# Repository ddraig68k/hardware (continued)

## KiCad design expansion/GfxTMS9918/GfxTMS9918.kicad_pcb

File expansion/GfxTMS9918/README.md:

# TMS9918 Video card

The TMS9918A is capable of a 256x192 pixel display with a 15 colour palette. It has 16K of video memory and 4 different video modes.

From the [Sega Retro](https://segaretro.org/TMS9918) site:

>There are 4 different screen modes available in the TMS9918A (as mentioned before, the TMS9918 lacks mode Graphic II):
>
>Mode 0 (Text): 40×24 characters monochrome. As the display is 256 pixels width, the character set is only 6 pixels wide. This mode doesn't support sprites, nor a separate border color setting.
>
>Mode 1 (Graphic 1): 32×24 characters (256×192 bitmap), where for each 8 characters in the character set the foreground and background color can be set. The chars "0"-"7" for example all have the same attributes.
>
>Mode 2 (Graphic 2): 32×24 characters (256×192 bitmap), with a 2-color limitation for each 8 pixel wide line inside a character.
>
>Mode 3 (Multicolor): 64×48 mode, very blocky and rarely used. Each 'pixel' can have its own color defined though, hence the name. Its sprites still have the same resolution as in screen modes 1 and 2.
>
>The TMS9918 has a fixed 16-color palette (actually 15 colors + transparent). 

The TMS9918A was designed to use DRAM, but I have used the design by [Leonardo Miliani](https://www.leonardomiliani.com/en/2019/lm80c-tms9918a/) that allows SRAM to be used instead.

The TMS9918 can also display up to 32 sprites (4 per scanline).

[Plasma effect on the TMS9918](https://www.youtube.com/watch?v=u6DVTGFEivY)

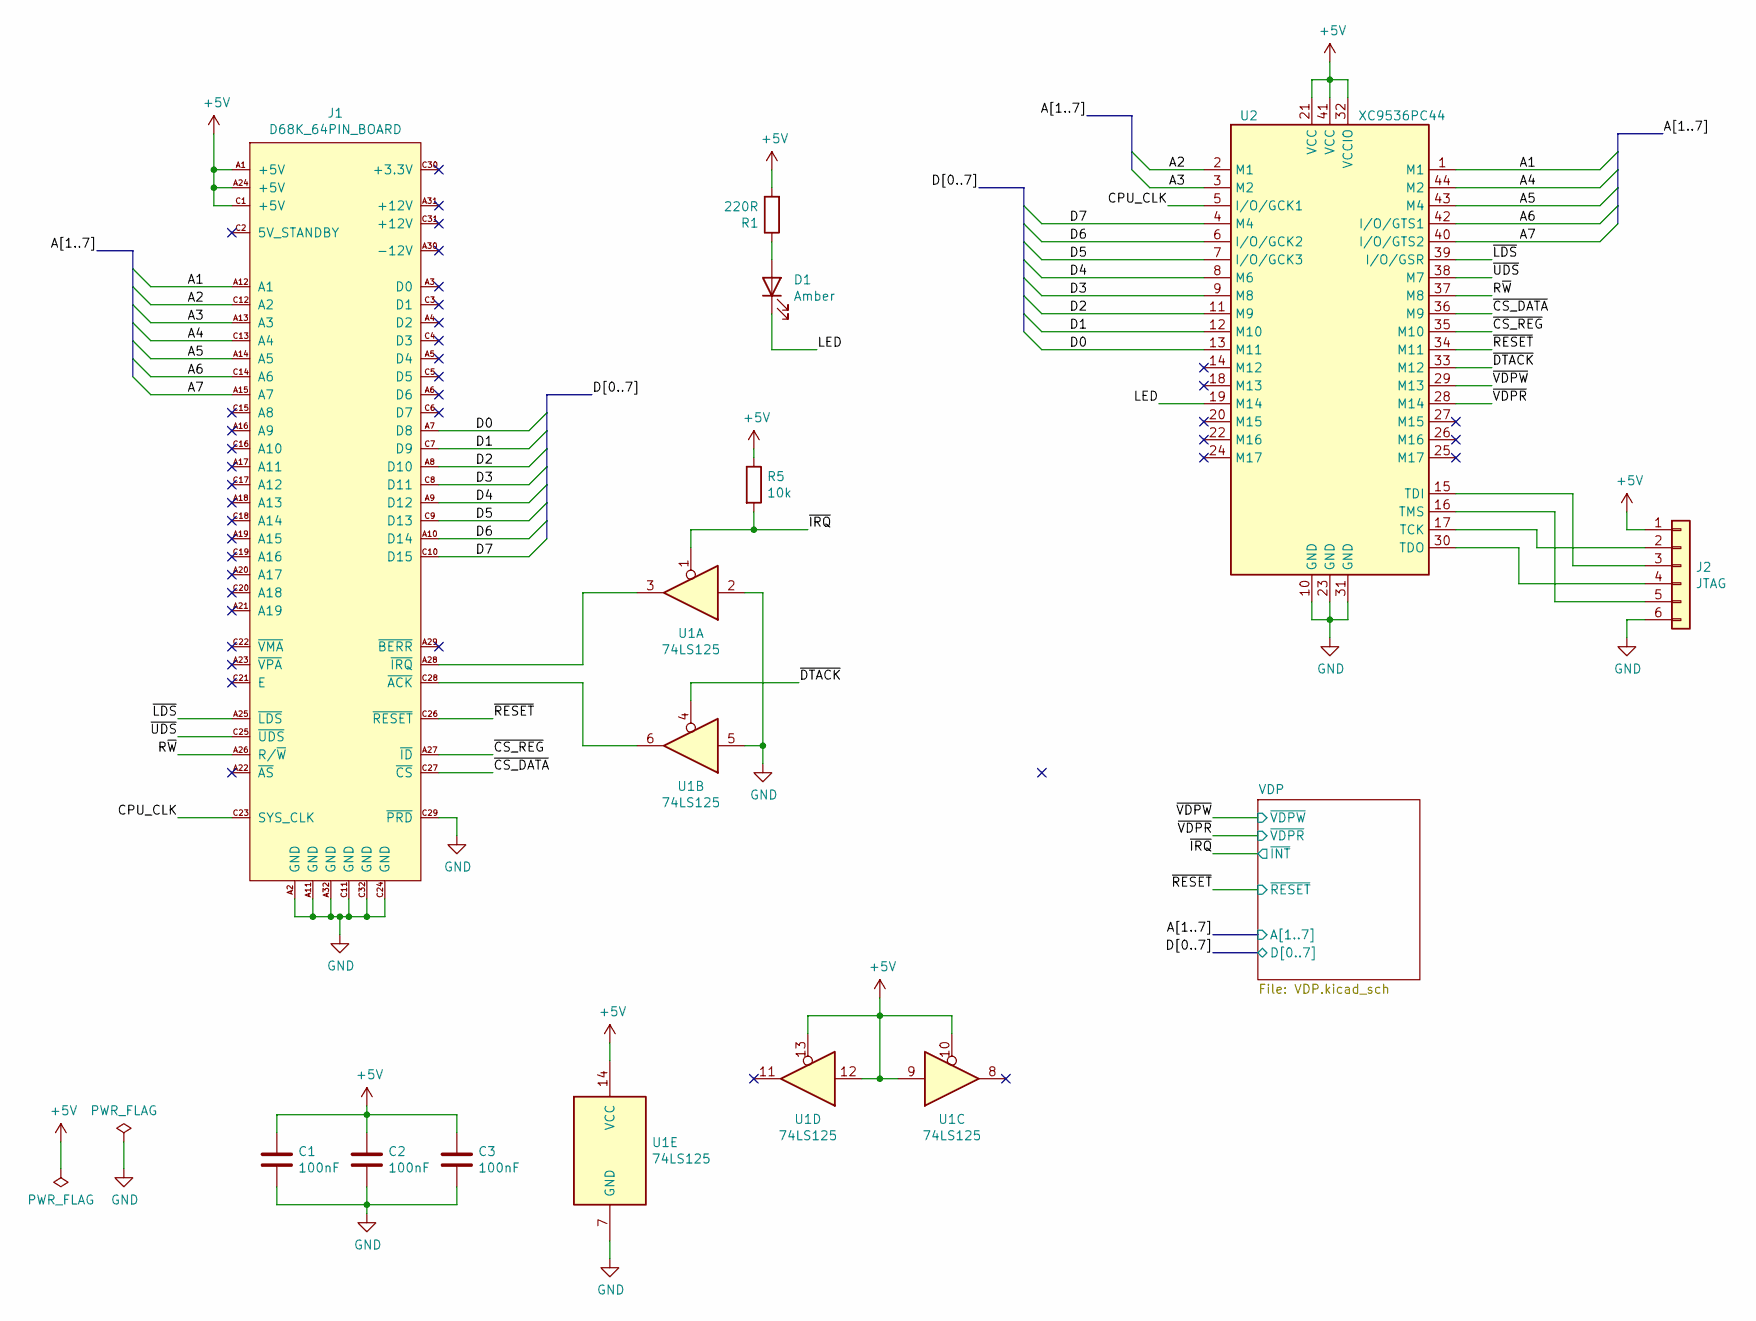
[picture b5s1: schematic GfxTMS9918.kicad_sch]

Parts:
C1, C2, C3: 100nF; C_Disc_D5.0mm_W2.5mm_P2.50mm
D1: Amber; LED_D5.0mm_FlatTop
J1: D68K_64PIN_BOARD; DIN41612_C_2x32_Male_Horizontal_THT
J2: JTAG; PinHeader_1x06_P2.54mm_Vertical
R1: 220R; R_Axial_DIN0207_L6.3mm_D2.5mm_P10.16mm_Horizontal
R5: 10k; R_Axial_DIN0207_L6.3mm_D2.5mm_P10.16mm_Horizontal
U1: 74LS125; DIP-14_W7.62mm_Socket
U2: XC9536PC44; PLCC-44_THT-Socket

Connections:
+5V: C1.1, C2.1, C3.1, J1.A1 (+5V), J1.A24 (+5V), J1.C1 (+5V), J2.1, R1.2, R5.1, U1.9, U1.10, U1.12, U1.13, U1.14 (VCC), U2.21 (VCC), U2.32 (VCCIO), U2.41 (VCC); also elsewhere on the board
/A1: J1.A12 (A1), U2.1 (M1); also elsewhere on the board
/A2: J1.C12 (A2), U2.2 (M1)
/A3: J1.A13 (A3), U2.3 (M2)
/A4: J1.C13 (A4), U2.44 (M2)
/A5: J1.A14 (A5), U2.43 (M4)
/A6: J1.C14 (A6), U2.42 (I/O/GTS1)
/A7: J1.A15 (A7), U2.40 (I/O/GTS2)
/CPU_CLK: J1.C23 (SYS_CLK), U2.5 (I/O/GCK1)
/D0: J1.A7 (D8), U2.13 (M11); also elsewhere on the board
/D1: J1.C7 (D9), U2.12 (M10); also elsewhere on the board
/D2: J1.A8 (D10), U2.11 (M9); also elsewhere on the board
/D3: J1.C8 (D11), U2.9 (M8); also elsewhere on the board
/D4: J1.A9 (D12), U2.8 (M6); also elsewhere on the board
/D5: J1.C9 (D13), U2.7 (I/O/GCK3); also elsewhere on the board
/D6: J1.A10 (D14), U2.6 (I/O/GCK2); also elsewhere on the board
/D7: J1.C10 (D15), U2.4 (M4); also elsewhere on the board
/LED: D1.1 (K), U2.19 (M14)
/R~W: J1.A26 (R/~W), U2.37 (M8)
/~CS_DATA: J1.C27 (~CS), U2.36 (M9)
/~CS_REG: J1.A27 (~ID), U2.35 (M10)
/~DTACK: U1.4, U2.33 (M12)
/~IRQ: R5.2, U1.1; also elsewhere on the board
/~LDS: J1.A25 (~LDS), U2.39 (I/O/GSR)
/~RESET: J1.C26 (~RESET), U2.34 (M11); also elsewhere on the board
/~UDS: J1.C25 (~UDS), U2.38 (M7)
/~VDPR: U2.28 (M14); also elsewhere on the board
/~VDPW: U2.29 (M13); also elsewhere on the board
GND: C1.2, C2.2, C3.2, J1.A2 (GND), J1.A11 (GND), J1.A32 (GND), J1.C11 (GND), J1.C24 (GND), J1.C29 (~PRD), J1.C32 (GND), J2.6, U1.2, U1.5, U1.7 (GND), U2.10 (GND), U2.23 (GND), U2.31 (GND); also elsewhere on the board
unnamed: D1.2 (A), R1.1
unnamed: J1.A28 (~IRQ), U1.3
unnamed: J1.C28 (~ACK), U1.6
unnamed: J2.2, U2.17 (TCK)
unnamed: J2.3, U2.15 (TDI)
unnamed: J2.4, U2.30 (TDO)
unnamed: J2.5, U2.16 (TMS)

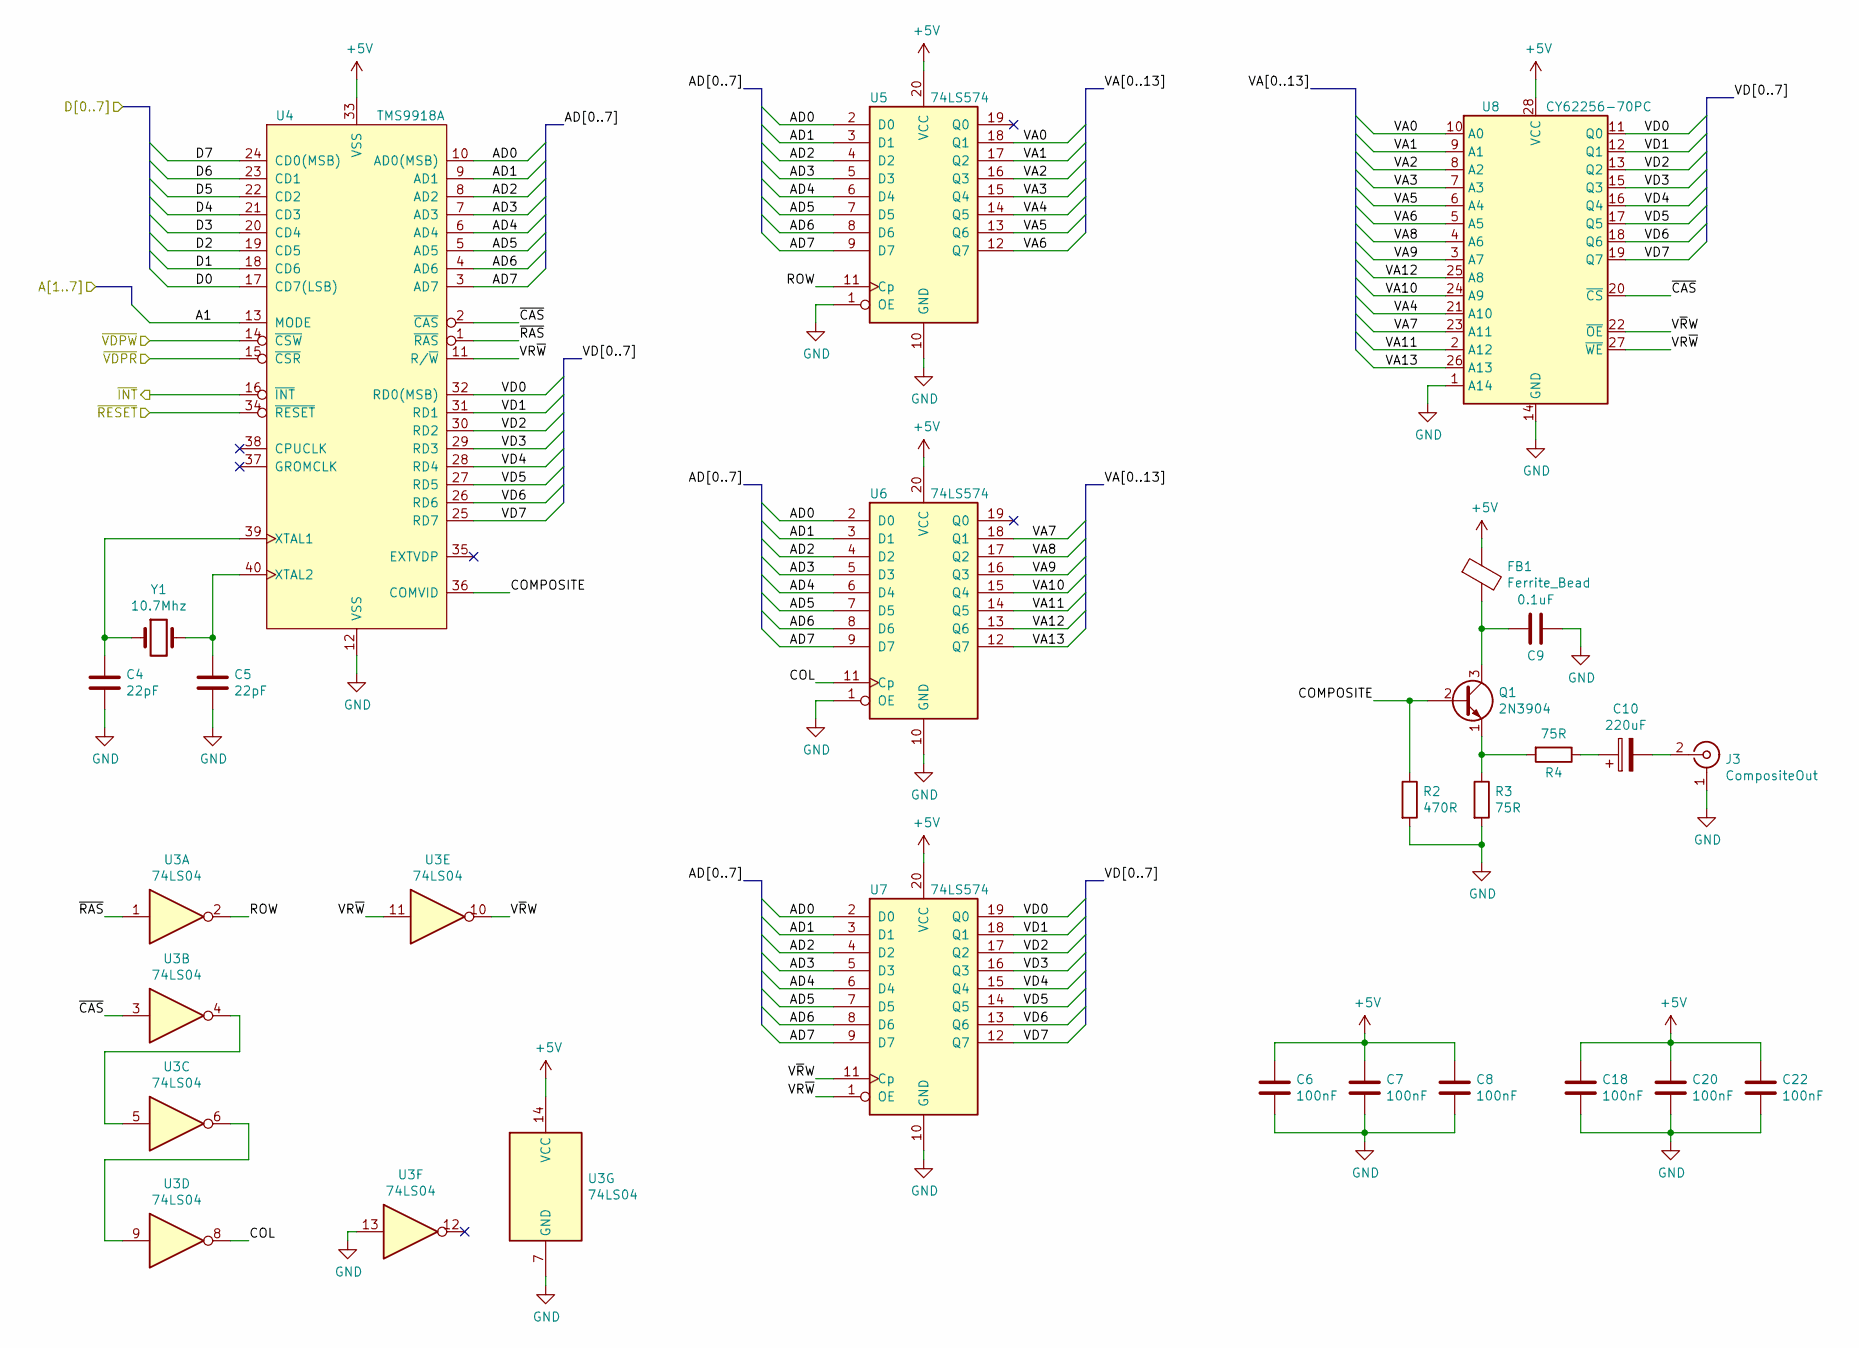
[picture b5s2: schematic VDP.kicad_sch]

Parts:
C4, C5: 22pF; C_Disc_D5.0mm_W2.5mm_P2.50mm
C6, C7, C8, C18, C20, C22: 100nF; C_Disc_D5.0mm_W2.5mm_P2.50mm
C9: 0.1uF; C_Disc_D5.0mm_W2.5mm_P2.50mm
C10: 220uF; CP_Radial_D5.0mm_P2.50mm
FB1: Ferrite_Bead; L_Axial_L6.6mm_D2.7mm_P10.16mm_Horizontal_Vishay_IM-2
J3: CompositeOut; KLPX0848A2RG
Q1: 2N3904; TO-92_Inline
R2: 470R; R_Axial_DIN0207_L6.3mm_D2.5mm_P10.16mm_Horizontal
R3, R4: 75R; R_Axial_DIN0207_L6.3mm_D2.5mm_P10.16mm_Horizontal
U3: 74LS04; DIP-14_W7.62mm_Socket
U4: TMS9918A; DIP-40_W15.24mm_Socket
U5, U6, U7: 74LS574; DIP-20_W7.62mm_Socket
U8: CY62256-70PC; DIP-28_W15.24mm
Y1: 10.7Mhz; Crystal_HC50_Vertical

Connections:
+5V: C6.1, C7.1, C8.1, C18.1, C20.1, C22.1, FB1.1, U3.14 (VCC), U4.33 (VSS), U5.20 (VCC), U6.20 (VCC), U7.20 (VCC), U8.28 (VCC); also elsewhere on the board
/A1: U4.13 (MODE); also elsewhere on the board
/D0: U4.17 (CD7(LSB)); also elsewhere on the board
/D1: U4.18 (CD6); also elsewhere on the board
/D2: U4.19 (CD5); also elsewhere on the board
/D3: U4.20 (CD4); also elsewhere on the board
/D4: U4.21 (CD3); also elsewhere on the board
/D5: U4.22 (CD2); also elsewhere on the board
/D6: U4.23 (CD1); also elsewhere on the board
/D7: U4.24 (CD0(MSB)); also elsewhere on the board
/VDP/AD0: U4.10 (AD0(MSB)), U5.2 (D0), U6.2 (D0), U7.2 (D0)
/VDP/AD1: U4.9 (AD1), U5.3 (D1), U6.3 (D1), U7.3 (D1)
/VDP/AD2: U4.8 (AD2), U5.4 (D2), U6.4 (D2), U7.4 (D2)
/VDP/AD3: U4.7 (AD3), U5.5 (D3), U6.5 (D3), U7.5 (D3)
/VDP/AD4: U4.6 (AD4), U5.6 (D4), U6.6 (D4), U7.6 (D4)
/VDP/AD5: U4.5 (AD5), U5.7 (D5), U6.7 (D5), U7.7 (D5)
/VDP/AD6: U4.4 (AD6), U5.8 (D6), U6.8 (D6), U7.8 (D6)
/VDP/AD7: U4.3 (AD7), U5.9 (D7), U6.9 (D7), U7.9 (D7)
/VDP/COL: U3.8, U6.11 (Cp)
/VDP/COMPOSITE: Q1.2 (B), R2.1, U4.36 (COMVID)
/VDP/ROW: U3.2, U5.11 (Cp)
/VDP/VA0: U5.18 (Q1), U8.10 (A0)
/VDP/VA1: U5.17 (Q2), U8.9 (A1)
/VDP/VA2: U5.16 (Q3), U8.8 (A2)
/VDP/VA3: U5.15 (Q4), U8.7 (A3)
/VDP/VA4: U5.14 (Q5), U8.21 (A10)
/VDP/VA5: U5.13 (Q6), U8.6 (A4)
/VDP/VA6: U5.12 (Q7), U8.5 (A5)
/VDP/VA7: U6.18 (Q1), U8.23 (A11)
/VDP/VA8: U6.17 (Q2), U8.4 (A6)
/VDP/VA9: U6.16 (Q3), U8.3 (A7)
/VDP/VA10: U6.15 (Q4), U8.24 (A9)
/VDP/VA11: U6.14 (Q5), U8.2 (A12)
/VDP/VA12: U6.13 (Q6), U8.25 (A8)
/VDP/VA13: U6.12 (Q7), U8.26 (A13)
/VDP/VD0: U4.32 (RD0(MSB)), U7.19 (Q0), U8.11 (Q0)
/VDP/VD1: U4.31 (RD1), U7.18 (Q1), U8.12 (Q1)
/VDP/VD2: U4.30 (RD2), U7.17 (Q2), U8.13 (Q2)
/VDP/VD3: U4.29 (RD3), U7.16 (Q3), U8.15 (Q3)
/VDP/VD4: U4.28 (RD4), U7.15 (Q4), U8.16 (Q4)
/VDP/VD5: U4.27 (RD5), U7.14 (Q5), U8.17 (Q5)
/VDP/VD6: U4.26 (RD6), U7.13 (Q6), U8.18 (Q6)
/VDP/VD7: U4.25 (RD7), U7.12 (Q7), U8.19 (Q7)
/VDP/VR~W: U3.11, U4.11 (R/~W), U7.1 (OE), U8.27 (~WE)
/VDP/V~RW: U3.10, U7.11 (Cp), U8.22 (~OE)
/VDP/~CAS: U3.3, U4.2 (~CAS), U8.20 (~CS)
/VDP/~RAS: U3.1, U4.1 (~RAS)
/~IRQ: U4.16 (~INT); also elsewhere on the board
/~RESET: U4.34 (~RESET); also elsewhere on the board
/~VDPR: U4.15 (~CSR); also elsewhere on the board
/~VDPW: U4.14 (~CSW); also elsewhere on the board
GND: C4.2, C5.2, C6.2, C7.2, C8.2, C9.1, C18.2, C20.2, C22.2, J3.1 (Ext), R2.2, R3.2, U3.7 (GND), U3.13, U4.12 (VSS), U5.1 (OE), U5.10 (GND), U6.1 (OE), U6.10 (GND), U7.10 (GND), U8.1 (A14), U8.14 (GND); also elsewhere on the board
unnamed: C4.1, U4.39 (XTAL1), Y1.1
unnamed: C5.1, U4.40 (XTAL2), Y1.2
unnamed: C9.2, FB1.2, Q1.3 (C)
unnamed: C10.1, R4.1
unnamed: C10.2, J3.2 (In)
unnamed: Q1.1 (E), R3.1, R4.2
unnamed: U3.4, U3.5
unnamed: U3.6, U3.9

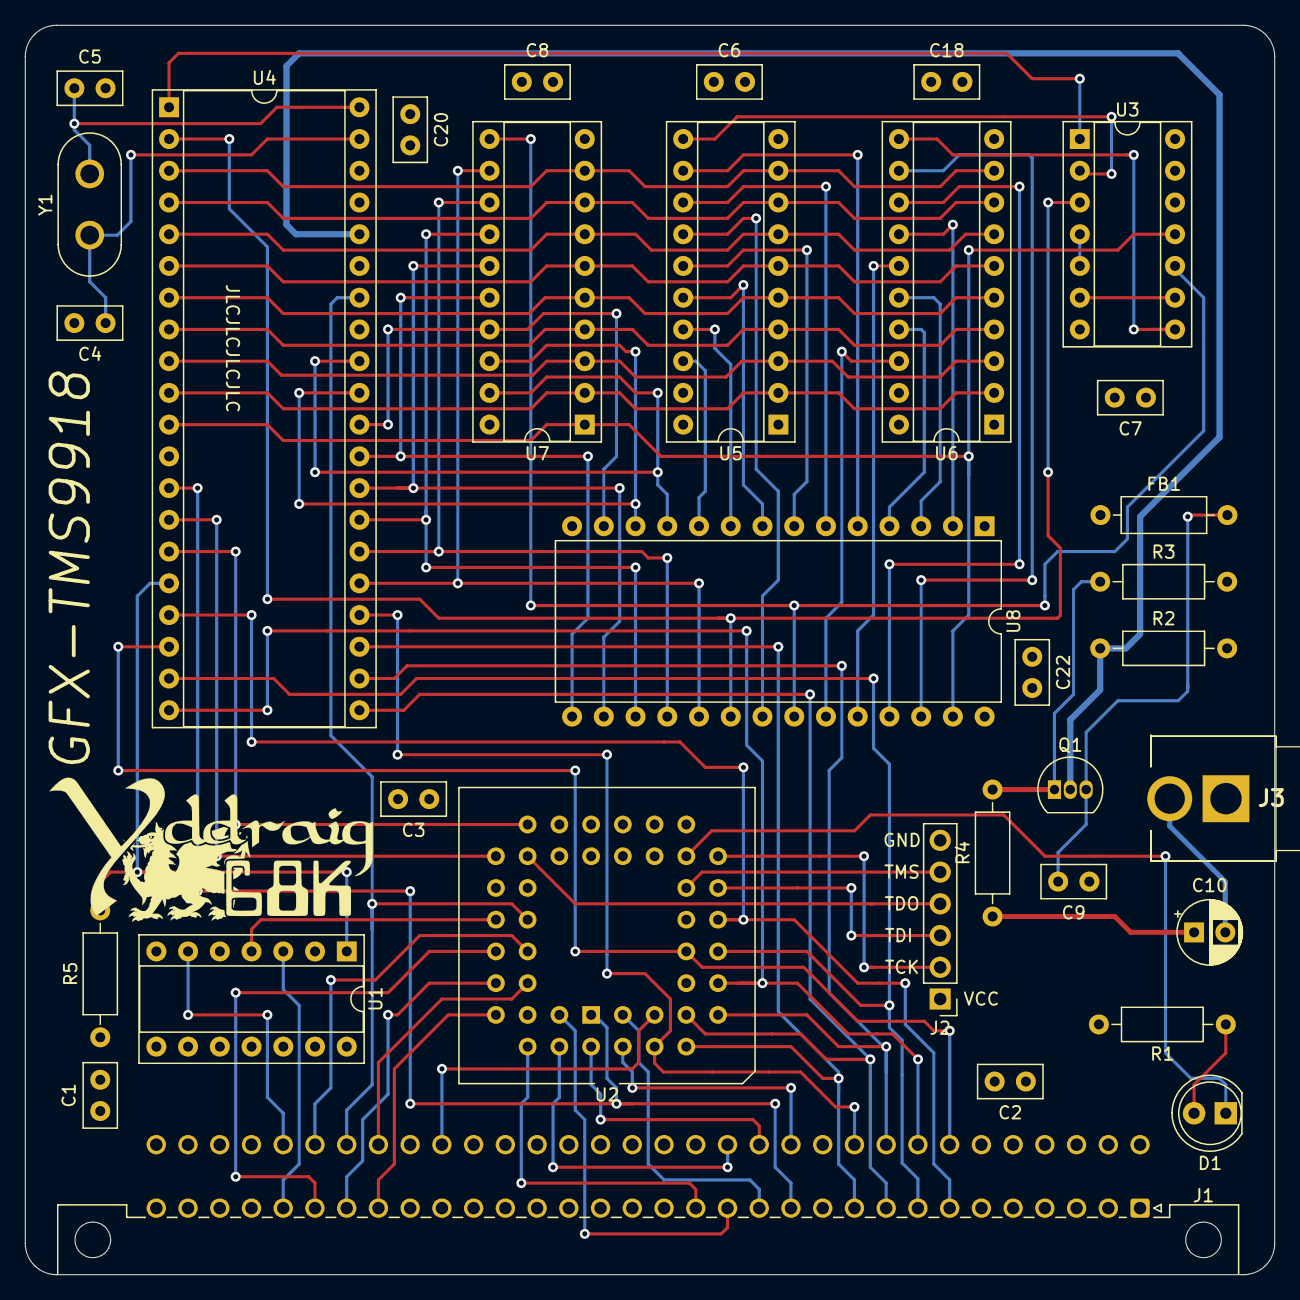
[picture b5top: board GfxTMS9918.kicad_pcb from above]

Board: 4 copper layers, 100.0 x 100.0 mm, 33 parts (0 on the bottom side), 81 nets.

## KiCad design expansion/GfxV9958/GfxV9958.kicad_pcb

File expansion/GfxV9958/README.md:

# V9958 Video Card

The Yamaha V9958 is the successor to the V9938 and TMS9918 that were commonly used in the MSX computer line with the V9958 appearing in the MSX2+. 

It has the following specifications:
* VRAM: 128 KB + 64 KB of expanded VRAM
* Text modes: 80 x 24 and 32 x 24
* Resolution: 512 x 212 (16 colors out of 512) and 256 x 212 (19268 colors)
* Sprites: 32, 16 colors, max 8 per horizontal line
* Hardware acceleration for copy, line, fill, etc.
* Interlacing to double vertical resolution
* Horizontal and vertical scroll registers 

The board has 3 different outputs. A composite output, S-Video output and a [Xrgb Mini RGB](https://www.retrorgb.com/retro-gaming-cables-now-offering-8pin-minidin-scart-cables.html) compatible 8-pin mini DIN output aimed at SCART use. There is also an optional audio jack input that can supply audio the 8-pin din output so TV speakers can be used rather than an external speaker.

The V9958 board has 192K of RAM installed and uses a CXA2075M encoder to provide the video output signals. 

**V9958 Text Mode**

**V9958 Mandelbrot**

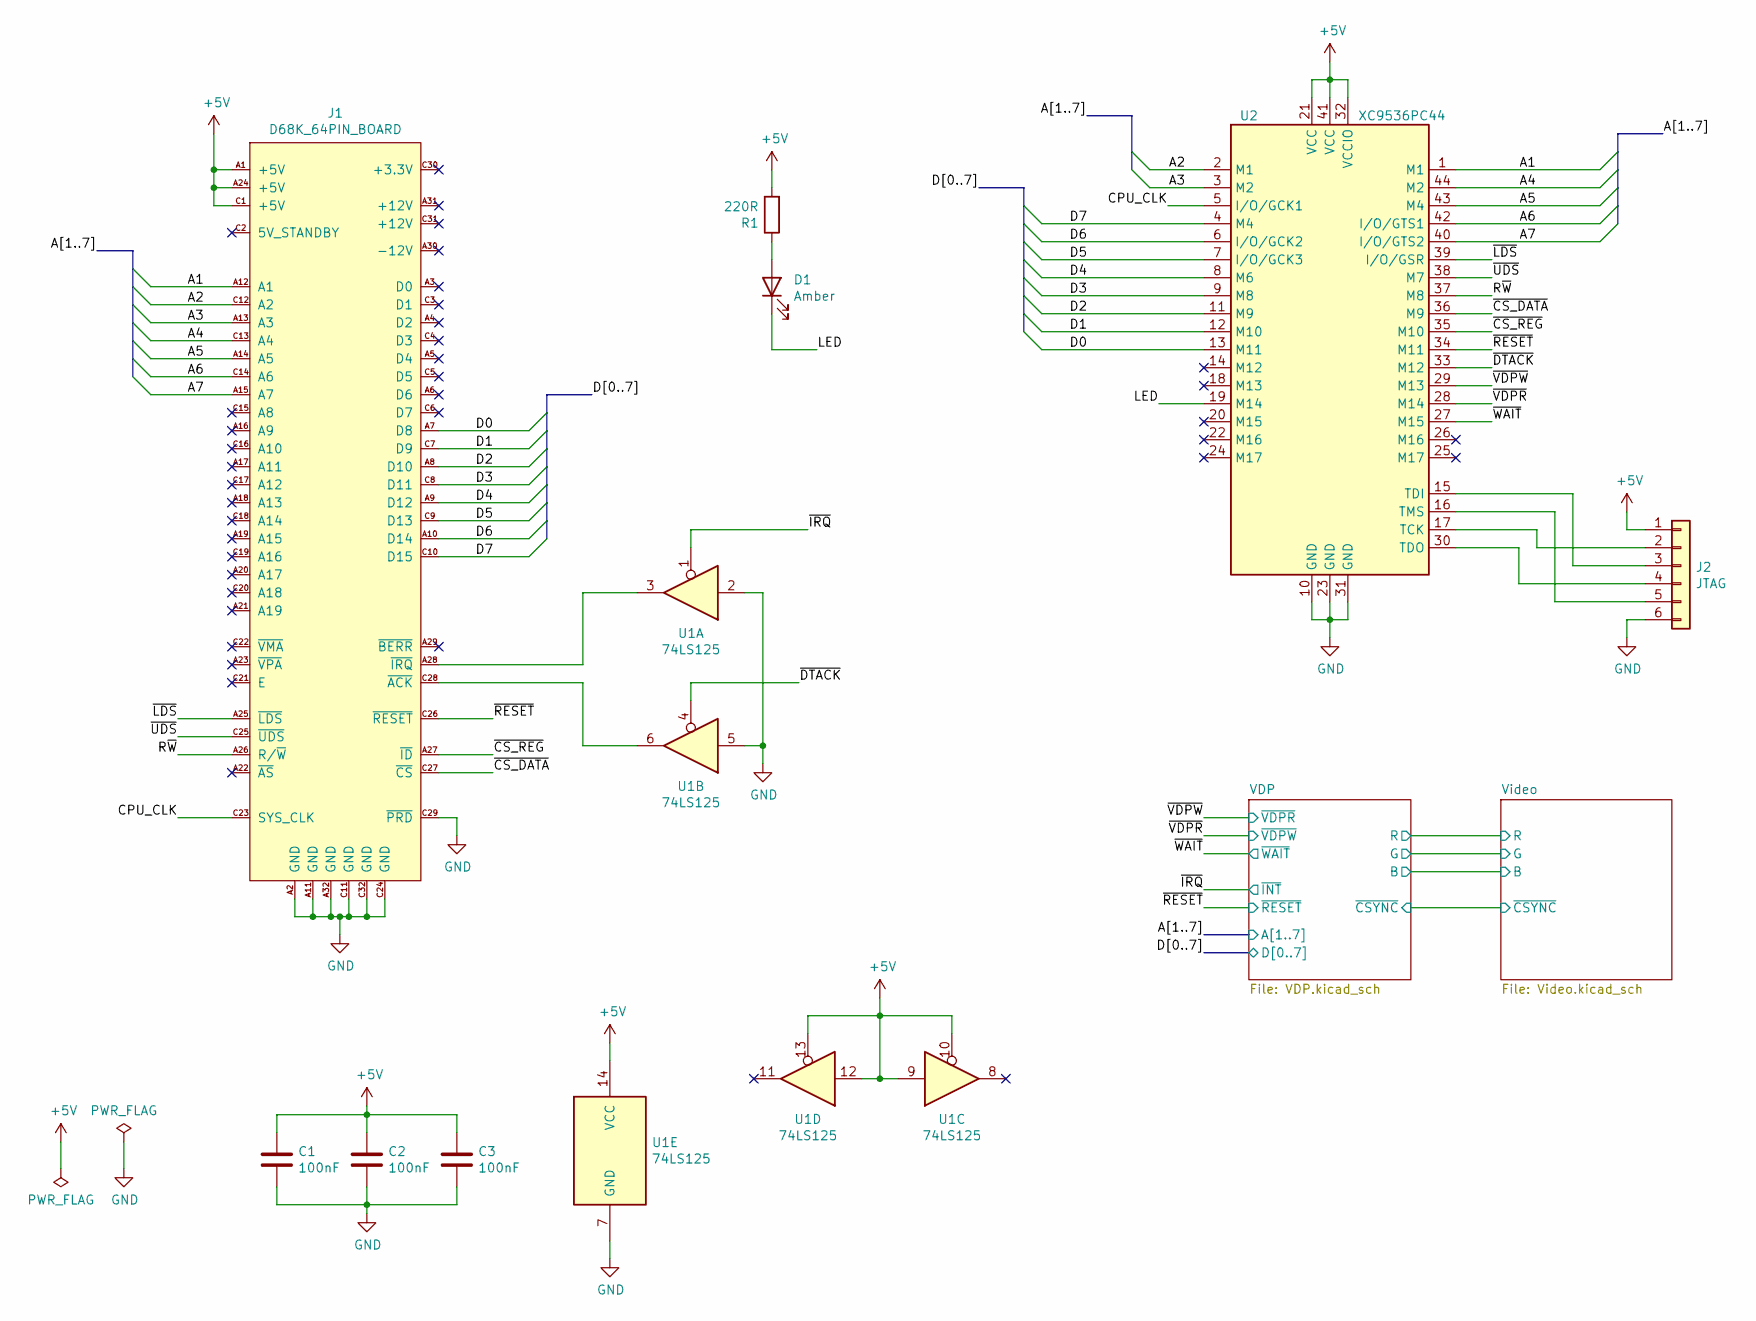
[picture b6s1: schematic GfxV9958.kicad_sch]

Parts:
C1, C2, C3: 100nF; C_Disc_D5.0mm_W2.5mm_P2.50mm
D1: Amber; LED_D5.0mm_FlatTop
J1: D68K_64PIN_BOARD; DIN41612_C_2x32_Male_Horizontal_THT
J2: JTAG; PinHeader_1x06_P2.54mm_Vertical
R1: 220R; R_Axial_DIN0207_L6.3mm_D2.5mm_P10.16mm_Horizontal
U1: 74LS125; DIP-14_W7.62mm_Socket
U2: XC9536PC44; PLCC-44_THT-Socket

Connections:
+5V: C1.1, C2.1, C3.1, J1.A1 (+5V), J1.A24 (+5V), J1.C1 (+5V), J2.1, R1.2, U1.9, U1.10, U1.12, U1.13, U1.14 (VCC), U2.21 (VCC), U2.32 (VCCIO), U2.41 (VCC); also elsewhere on the board
/A1: J1.A12 (A1), U2.1 (M1); also elsewhere on the board
/A2: J1.C12 (A2), U2.2 (M1); also elsewhere on the board
/A3: J1.A13 (A3), U2.3 (M2)
/A4: J1.C13 (A4), U2.44 (M2)
/A5: J1.A14 (A5), U2.43 (M4)
/A6: J1.C14 (A6), U2.42 (I/O/GTS1)
/A7: J1.A15 (A7), U2.40 (I/O/GTS2)
/CPU_CLK: J1.C23 (SYS_CLK), U2.5 (I/O/GCK1)
/D0: J1.A7 (D8), U2.13 (M11); also elsewhere on the board
/D1: J1.C7 (D9), U2.12 (M10); also elsewhere on the board
/D2: J1.A8 (D10), U2.11 (M9); also elsewhere on the board
/D3: J1.C8 (D11), U2.9 (M8); also elsewhere on the board
/D4: J1.A9 (D12), U2.8 (M6); also elsewhere on the board
/D5: J1.C9 (D13), U2.7 (I/O/GCK3); also elsewhere on the board
/D6: J1.A10 (D14), U2.6 (I/O/GCK2); also elsewhere on the board
/D7: J1.C10 (D15), U2.4 (M4); also elsewhere on the board
/LED: D1.1 (K), U2.19 (M14)
/R~W: J1.A26 (R/~W), U2.37 (M8)
/~CS_DATA: J1.C27 (~CS), U2.36 (M9)
/~CS_REG: J1.A27 (~ID), U2.35 (M10)
/~DTACK: U1.4, U2.33 (M12)
/~IRQ: U1.1; also elsewhere on the board
/~LDS: J1.A25 (~LDS), U2.39 (I/O/GSR)
/~RESET: J1.C26 (~RESET), U2.34 (M11); also elsewhere on the board
/~UDS: J1.C25 (~UDS), U2.38 (M7)
/~VDPR: U2.28 (M14); also elsewhere on the board
/~VDPW: U2.29 (M13); also elsewhere on the board
/~WAIT: U2.27 (M15); also elsewhere on the board
GND: C1.2, C2.2, C3.2, J1.A2 (GND), J1.A11 (GND), J1.A32 (GND), J1.C11 (GND), J1.C24 (GND), J1.C29 (~PRD), J1.C32 (GND), J2.6, U1.2, U1.5, U1.7 (GND), U2.10 (GND), U2.23 (GND), U2.31 (GND); also elsewhere on the board
unnamed: D1.2 (A), R1.1
unnamed: J1.A28 (~IRQ), U1.3
unnamed: J1.C28 (~ACK), U1.6
unnamed: J2.2, U2.17 (TCK)
unnamed: J2.3, U2.15 (TDI)
unnamed: J2.4, U2.30 (TDO)
unnamed: J2.5, U2.16 (TMS)

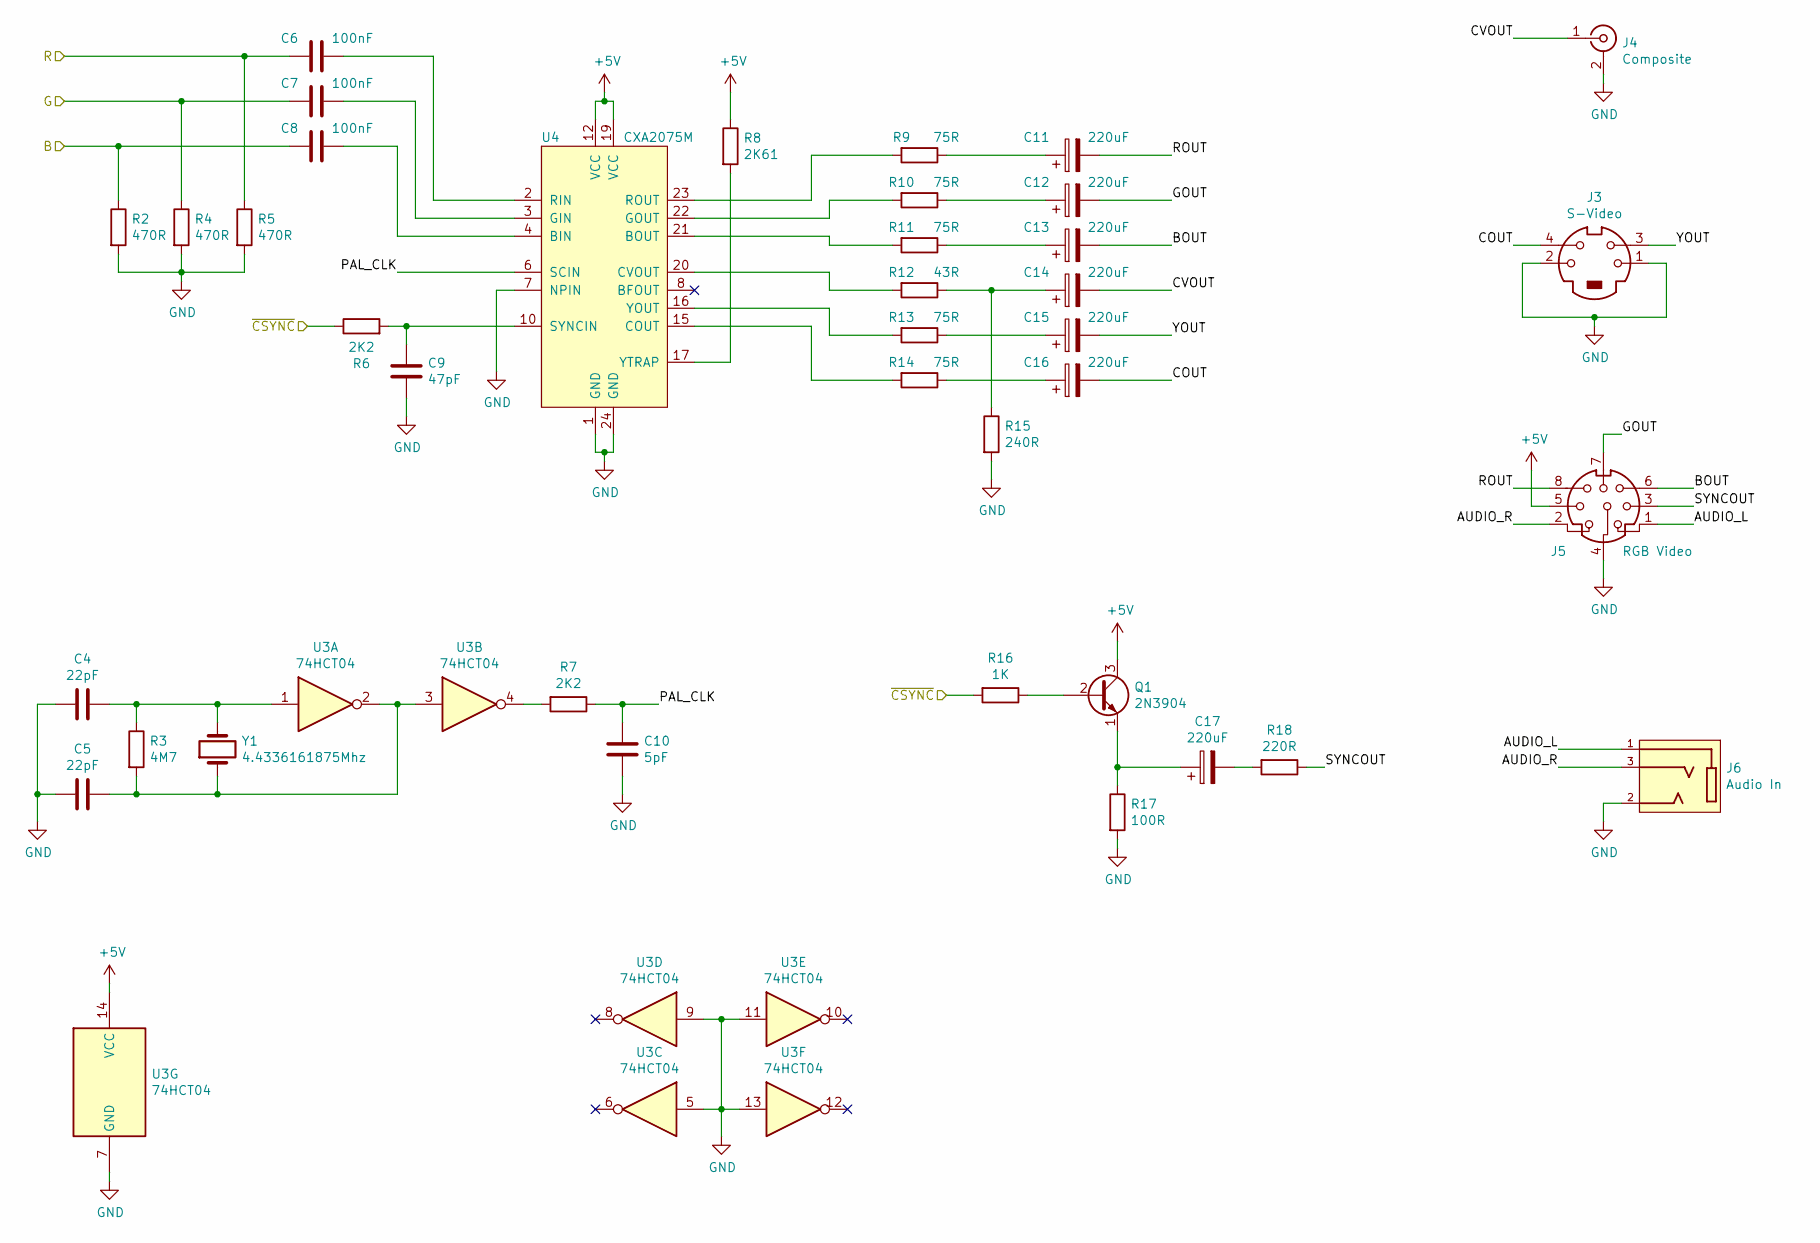
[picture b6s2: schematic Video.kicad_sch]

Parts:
C4, C5: 22pF; C_Disc_D5.0mm_W2.5mm_P2.50mm
C6, C7, C8: 100nF; C_Disc_D5.0mm_W2.5mm_P2.50mm
C9: 47pF; C_Disc_D5.0mm_W2.5mm_P2.50mm
C10: 5pF; C_Disc_D5.0mm_W2.5mm_P2.50mm
C11, C12, C13, C14, C15, C16, C17: 220uF; CP_Radial_D5.0mm_P2.50mm
J3: S-Video; MINI-DIN-4-TE_5749181-1
J4: Composite; KLPX0848A2RG
J5: RGB Video; MINI-DIN-8-TE_57492681
J6: Audio In; SWITCHCRAFT_35RAPC2BHN2; PARTREV L
Q1: 2N3904; TO-92_Inline
R2, R4, R5: 470R; R_Axial_DIN0207_L6.3mm_D2.5mm_P10.16mm_Horizontal
R3: 4M7; R_Axial_DIN0207_L6.3mm_D2.5mm_P10.16mm_Horizontal
R6, R7: 2K2; R_Axial_DIN0207_L6.3mm_D2.5mm_P10.16mm_Horizontal
R8: 2K61; R_Axial_DIN0207_L6.3mm_D2.5mm_P10.16mm_Horizontal
R9, R10, R11, R13, R14: 75R; R_Axial_DIN0207_L6.3mm_D2.5mm_P10.16mm_Horizontal
R12: 43R; R_Axial_DIN0207_L6.3mm_D2.5mm_P10.16mm_Horizontal
R15: 240R; R_Axial_DIN0207_L6.3mm_D2.5mm_P10.16mm_Horizontal
R16: 1K; R_Axial_DIN0207_L6.3mm_D2.5mm_P10.16mm_Horizontal
R17: 100R; R_Axial_DIN0207_L6.3mm_D2.5mm_P10.16mm_Horizontal
R18: 220R; R_Axial_DIN0207_L6.3mm_D2.5mm_P10.16mm_Horizontal
U3: 74HCT04; DIP-14_W7.62mm_Socket
U4: CXA2075M; SOP-24_7.5x15.4mm_P1.27mm
Y1: 4.4336161875Mhz; Crystal_HC50_Vertical

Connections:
+5V: J5.5, Q1.3 (C), R8.1, U3.14 (VCC), U4.12 (VCC), U4.19 (VCC); also elsewhere on the board
/VDP/B: C8.2, R2.1; also elsewhere on the board
/VDP/G: C7.2, R4.1; also elsewhere on the board
/VDP/R: C6.2, R5.1; also elsewhere on the board
/VDP/~CSYNC: R6.1, R16.2; also elsewhere on the board
/Video/AUDIO_L: J5.1, J6.1
/Video/AUDIO_R: J5.2, J6.3
/Video/BOUT: C13.2, J5.6
/Video/COUT: C16.2, J3.4
/Video/CVOUT: C14.2, J4.1 (In)
/Video/GOUT: C12.2, J5.7
/Video/PAL_CLK: C10.1, R7.1, U4.6 (SCIN)
/Video/ROUT: C11.2, J5.8
/Video/SYNCOUT: J5.3, R18.1
/Video/YOUT: C15.2, J3.3
GND: C4.2, C5.2, C9.2, C10.2, J3.1, J3.2, J4.2 (Ext), J5.4, J6.2, R2.2, R4.2, R5.2, R15.2, R17.2, U3.5, U3.7 (GND), U3.9, U3.11, U3.13, U4.1 (GND), U4.7 (NPIN), U4.24 (GND); also elsewhere on the board
unnamed: C4.1, R3.1, U3.1, Y1.2
unnamed: C5.1, R3.2, U3.2, U3.3, Y1.1
unnamed: C6.1, U4.2 (RIN)
unnamed: C7.1, U4.3 (GIN)
unnamed: C8.1, U4.4 (BIN)
unnamed: C9.1, R6.2, U4.10 (SYNCIN)
unnamed: C11.1, R9.1
unnamed: C12.1, R10.1
unnamed: C13.1, R11.1
unnamed: C14.1, R12.1, R15.1
unnamed: C15.1, R13.1
unnamed: C16.1, R14.1
unnamed: C17.1, Q1.1 (E), R17.1
unnamed: C17.2, R18.2
unnamed: Q1.2 (B), R16.1
unnamed: R7.2, U3.4
unnamed: R8.2, U4.17 (YTRAP)
unnamed: R9.2, U4.23 (ROUT)
unnamed: R10.2, U4.22 (GOUT)
unnamed: R11.2, U4.21 (BOUT)
unnamed: R12.2, U4.20 (CVOUT)
unnamed: R13.2, U4.16 (YOUT)
unnamed: R14.2, U4.15 (COUT)

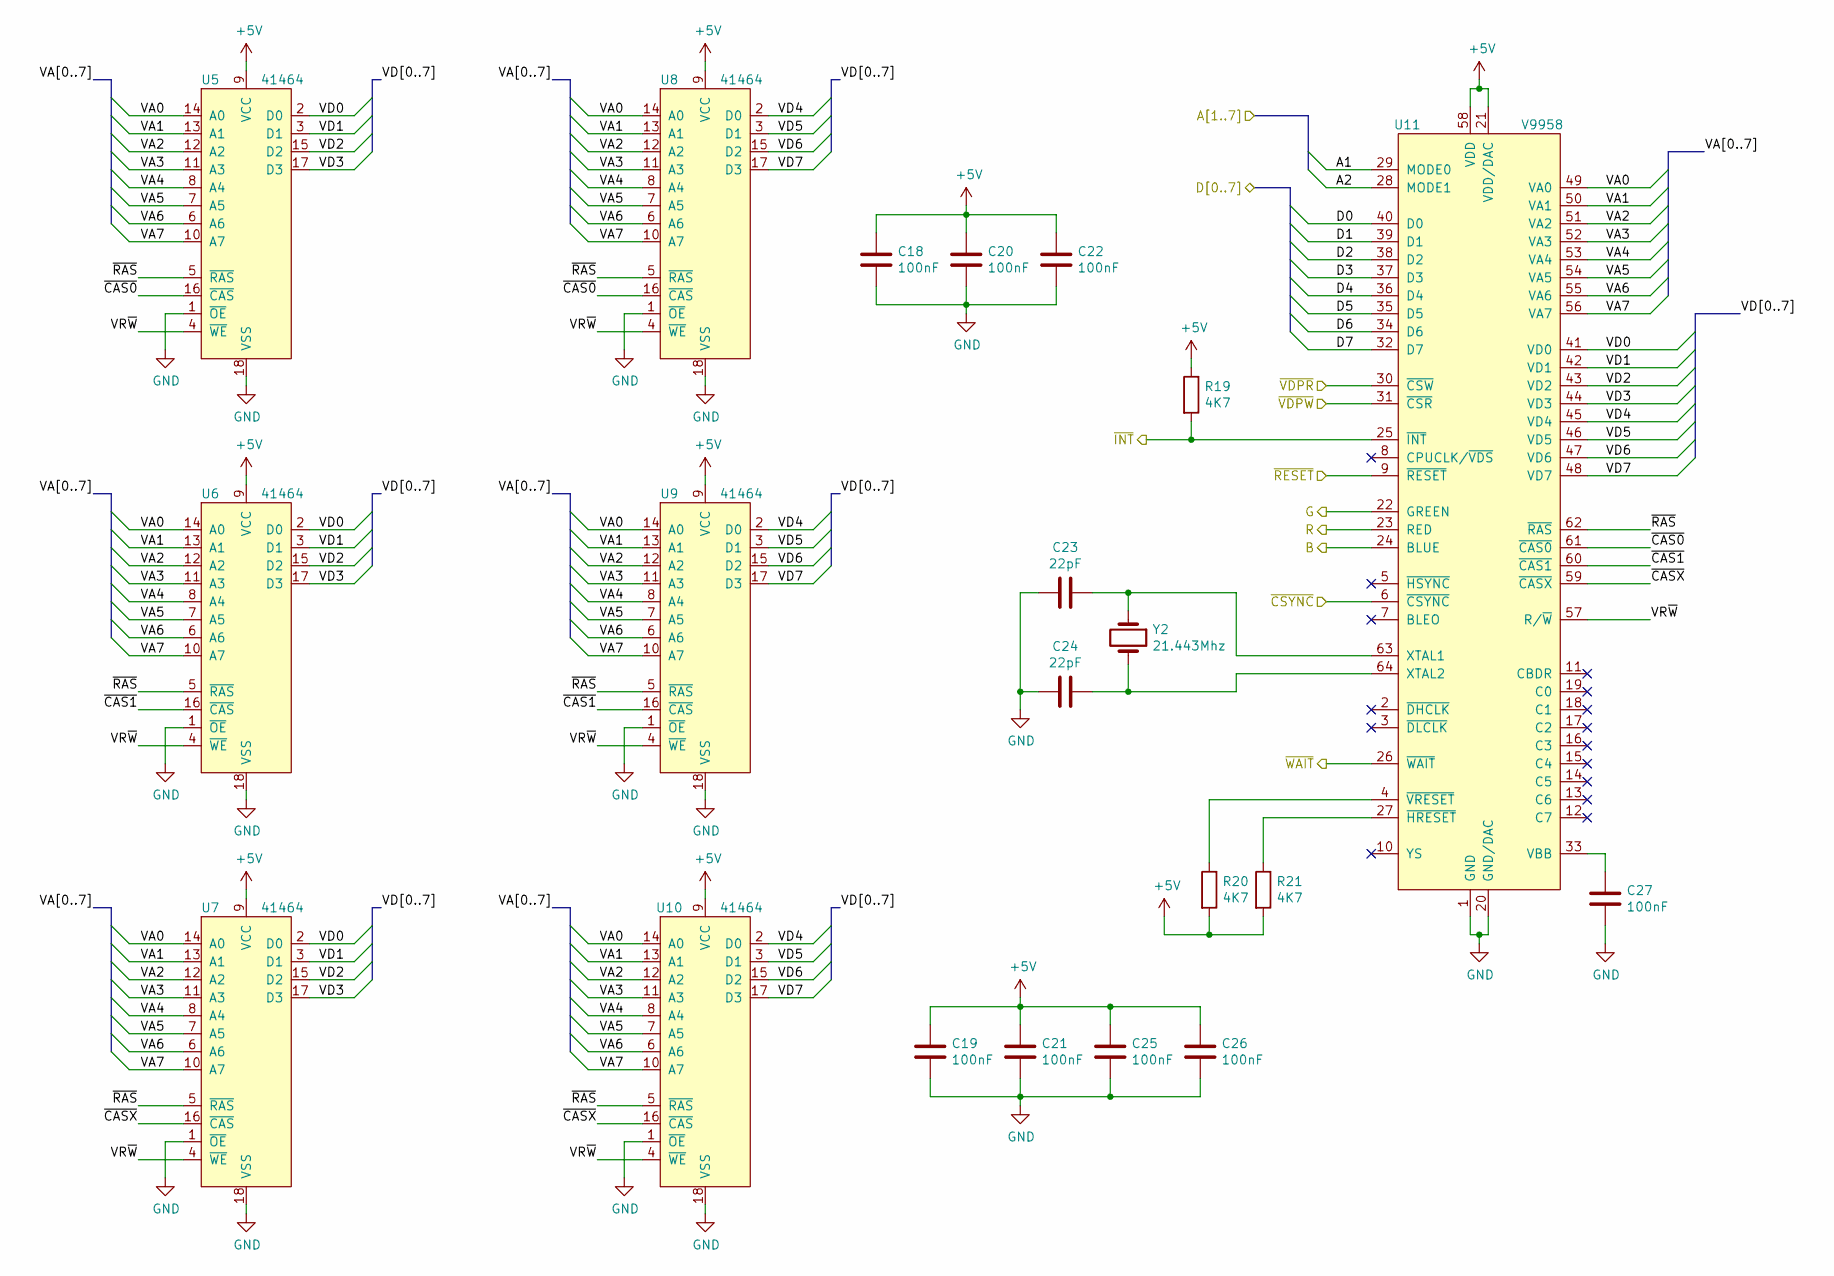
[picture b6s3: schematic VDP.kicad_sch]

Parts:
C18, C19, C20, C21, C22, C25, C26, C27: 100nF; C_Disc_D5.0mm_W2.5mm_P2.50mm
C23, C24: 22pF; C_Disc_D5.0mm_W2.5mm_P2.50mm
R19, R20, R21: 4K7; R_Axial_DIN0207_L6.3mm_D2.5mm_P10.16mm_Horizontal
U5, U6, U7, U8, U9, U10: 41464; DIP-18_W7.62mm_Socket
U11: V9958; DIP-64-V9958
Y2: 21.443Mhz; Crystal_HC50_Vertical

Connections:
+5V: C18.1, C19.1, C20.1, C21.1, C22.1, C25.1, C26.1, R19.1, R20.2, R21.2, U5.9 (VCC), U6.9 (VCC), U7.9 (VCC), U8.9 (VCC), U9.9 (VCC), U10.9 (VCC), U11.21 (VDD/DAC), U11.58 (VDD); also elsewhere on the board
/A1: U11.29 (MODE0); also elsewhere on the board
/A2: U11.28 (MODE1); also elsewhere on the board
/D0: U11.40 (D0); also elsewhere on the board
/D1: U11.39 (D1); also elsewhere on the board
/D2: U11.38 (D2); also elsewhere on the board
/D3: U11.37 (D3); also elsewhere on the board
/D4: U11.36 (D4); also elsewhere on the board
/D5: U11.35 (D5); also elsewhere on the board
/D6: U11.34 (D6); also elsewhere on the board
/D7: U11.32 (D7); also elsewhere on the board
/VDP/B: U11.24 (BLUE); also elsewhere on the board
/VDP/G: U11.22 (GREEN); also elsewhere on the board
/VDP/R: U11.23 (RED); also elsewhere on the board
/VDP/VA0: U5.14 (A0), U6.14 (A0), U7.14 (A0), U8.14 (A0), U9.14 (A0), U10.14 (A0), U11.49 (VA0)
/VDP/VA1: U5.13 (A1), U6.13 (A1), U7.13 (A1), U8.13 (A1), U9.13 (A1), U10.13 (A1), U11.50 (VA1)
/VDP/VA2: U5.12 (A2), U6.12 (A2), U7.12 (A2), U8.12 (A2), U9.12 (A2), U10.12 (A2), U11.51 (VA2)
/VDP/VA3: U5.11 (A3), U6.11 (A3), U7.11 (A3), U8.11 (A3), U9.11 (A3), U10.11 (A3), U11.52 (VA3)
/VDP/VA4: U5.8 (A4), U6.8 (A4), U7.8 (A4), U8.8 (A4), U9.8 (A4), U10.8 (A4), U11.53 (VA4)
/VDP/VA5: U5.7 (A5), U6.7 (A5), U7.7 (A5), U8.7 (A5), U9.7 (A5), U10.7 (A5), U11.54 (VA5)
/VDP/VA6: U5.6 (A6), U6.6 (A6), U7.6 (A6), U8.6 (A6), U9.6 (A6), U10.6 (A6), U11.55 (VA6)
/VDP/VA7: U5.10 (A7), U6.10 (A7), U7.10 (A7), U8.10 (A7), U9.10 (A7), U10.10 (A7), U11.56 (VA7)
/VDP/VD0: U5.2 (D0), U6.2 (D0), U7.2 (D0), U11.41 (VD0)
/VDP/VD1: U5.3 (D1), U6.3 (D1), U7.3 (D1), U11.42 (VD1)
/VDP/VD2: U5.15 (D2), U6.15 (D2), U7.15 (D2), U11.43 (VD2)
/VDP/VD3: U5.17 (D3), U6.17 (D3), U7.17 (D3), U11.44 (VD3)
/VDP/VD4: U8.2 (D0), U9.2 (D0), U10.2 (D0), U11.45 (VD4)
/VDP/VD5: U8.3 (D1), U9.3 (D1), U10.3 (D1), U11.46 (VD5)
/VDP/VD6: U8.15 (D2), U9.15 (D2), U10.15 (D2), U11.47 (VD6)
/VDP/VD7: U8.17 (D3), U9.17 (D3), U10.17 (D3), U11.48 (VD7)
/VDP/VR~W: U5.4 (~WE), U6.4 (~WE), U7.4 (~WE), U8.4 (~WE), U9.4 (~WE), U10.4 (~WE), U11.57 (R/~W)
/VDP/~CAS0: U5.16 (~CAS), U8.16 (~CAS), U11.61 (~CAS0)
/VDP/~CAS1: U6.16 (~CAS), U9.16 (~CAS), U11.60 (~CAS1)
/VDP/~CASX: U7.16 (~CAS), U10.16 (~CAS), U11.59 (~CASX)
/VDP/~CSYNC: U11.6 (~CSYNC); also elsewhere on the board
/VDP/~RAS: U5.5 (~RAS), U6.5 (~RAS), U7.5 (~RAS), U8.5 (~RAS), U9.5 (~RAS), U10.5 (~RAS), U11.62 (~RAS)
/~IRQ: R19.2, U11.25 (~INT); also elsewhere on the board
/~RESET: U11.9 (~RESET); also elsewhere on the board
/~VDPR: U11.31 (~CSR); also elsewhere on the board
/~VDPW: U11.30 (~CSW); also elsewhere on the board
/~WAIT: U11.26 (~WAIT); also elsewhere on the board
GND: C18.2, C19.2, C20.2, C21.2, C22.2, C23.2, C24.2, C25.2, C26.2, C27.2, U5.1 (~OE), U5.18 (VSS), U6.1 (~OE), U6.18 (VSS), U7.1 (~OE), U7.18 (VSS), U8.1 (~OE), U8.18 (VSS), U9.1 (~OE), U9.18 (VSS), U10.1 (~OE), U10.18 (VSS), U11.1 (GND), U11.20 (GND/DAC); also elsewhere on the board
unnamed: C23.1, U11.63 (XTAL1), Y2.1
unnamed: C24.1, U11.64 (XTAL2), Y2.2
unnamed: C27.1, U11.33 (VBB)
unnamed: R20.1, U11.4 (~VRESET)
unnamed: R21.1, U11.27 (~HRESET)
